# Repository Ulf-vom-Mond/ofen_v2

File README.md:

# Ofen v2
This is a project about building an oven for high temperatures. Included in this repository are the schematics and the layout for the control PCB and the microcontroller firmware.

## Building with Arduino IDE
You need to install the following libraries:

### LCDWiki library
This is neccessary for SPI communication with the ILI9488 LCD driver.
Follow this page for installation: http://www.lcdwiki.com/3.5inch_SPI_Module_ILI9488_SKU:MSP3520

### MiniCore
The schematic uses a bare ATMega328p without the Arduino overhead. For an effective use of all its features, you need to follow this installation guide:
https://github.com/MCUdude/MiniCore

IMPORTANT: You need to set the clock to "Internal 8 MHz". If you select anything called "external", the ATMega will not run and you cannot program it anymore.

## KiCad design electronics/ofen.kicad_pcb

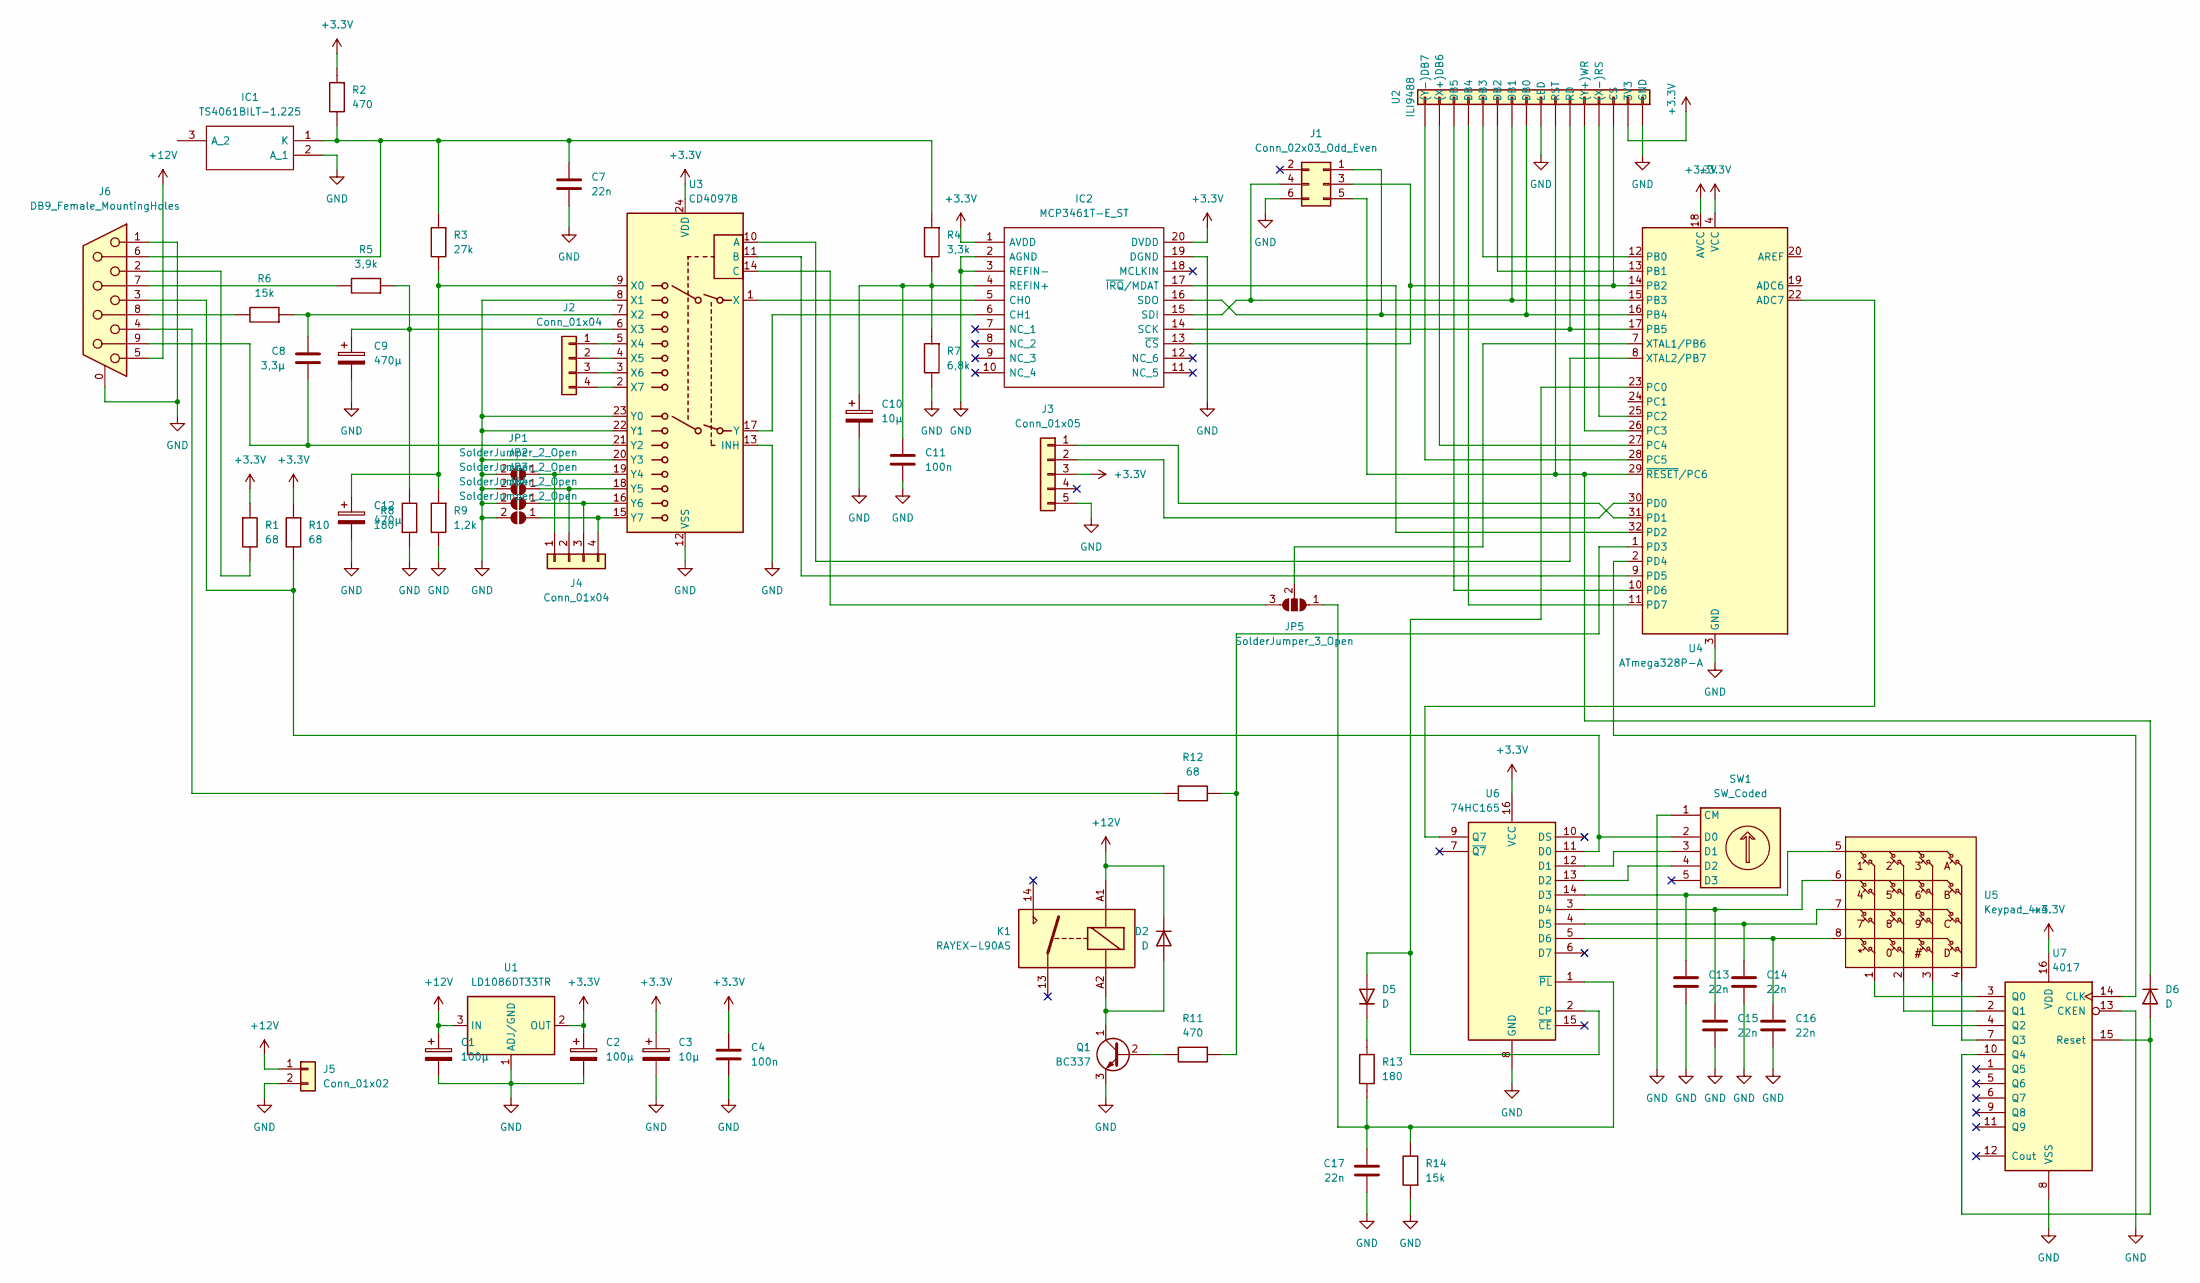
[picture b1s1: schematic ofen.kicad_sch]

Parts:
C1, C2: 100µ; CP_Radial_D6.3mm_P2.50mm
C3, C10: 10µ; CP_Radial_Tantal_D4.5mm_P5.00mm
C4, C11: 100n; C_Rect_L10.0mm_W4.0mm_P7.50mm_MKS4
C7, C13, C14, C15, C16, C17: 22n; C_Disc_D5.0mm_W2.5mm_P2.50mm
C8: 3,3µ; C_Rect_L7.2mm_W7.2mm_P5.00mm_FKS2_FKP2_MKS2_MKP2
C9, C12: 470µ; CP_Radial_D10.0mm_P5.00mm
D2, D5, D6: D; D_A-405_P7.62mm_Horizontal
IC1: TS4061BILT-1.225; SOT-23-3; Mouser Part Number 511-TS4061BILT-1.225
IC2: MCP3461T-E_ST; TSSOP-20_4.4x6.5mm_P0.65mm; Mouser Part Number 579-MCP3461T-E/ST
J1: Conn_02x03_Odd_Even; IDC-Header_2x03_P2.54mm_Vertical
J2, J4: Conn_01x04; PinHeader_1x04_P2.54mm_Vertical
J3: Conn_01x05; PinSocket_1x05_P2.54mm_Vertical
J5: Conn_01x02; JST_VH_B2P3-VH_1x02_P7.92mm_Vertical
J6: DB9_Female_MountingHoles; DSUB-9_Female_Horizontal_P2.77x2.84mm_EdgePinOffset7.70mm_H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
JP1, JP2, JP3, JP4: SolderJumper_2_Open; SolderJumper-2_P1.3mm_Open_RoundedPad1.0x1.5mm
JP5: SolderJumper_3_Open; SolderJumper-3_P1.3mm_Open_RoundedPad1.0x1.5mm_NumberLabels
K1: RAYEX-L90AS; Relay_SPST_RAYEX-L90AS
Q1: BC337; TO-92_Inline_Wide
R1, R10, R12: 68; R_Axial_DIN0207_L6.3mm_D2.5mm_P10.16mm_Horizontal
R2, R11: 470; R_Axial_DIN0207_L6.3mm_D2.5mm_P10.16mm_Horizontal
R3: 27k; R_Axial_DIN0207_L6.3mm_D2.5mm_P10.16mm_Horizontal
R4: 3,3k; R_Axial_DIN0207_L6.3mm_D2.5mm_P10.16mm_Horizontal
R5: 3,9k; R_Axial_DIN0207_L6.3mm_D2.5mm_P10.16mm_Horizontal
R6, R14: 15k; R_Axial_DIN0207_L6.3mm_D2.5mm_P10.16mm_Horizontal
R7: 6,8k; R_Axial_DIN0207_L6.3mm_D2.5mm_P10.16mm_Horizontal
R8, R13: 180; R_Axial_DIN0207_L6.3mm_D2.5mm_P10.16mm_Horizontal
R9: 1,2k; R_Axial_DIN0207_L6.3mm_D2.5mm_P10.16mm_Horizontal
SW1: SW_Coded; PinHeader_1x04_P2.54mm_Vertical
U1: LD1086DT33TR; SOT-223-3_TabPin2
U2: ILI9488; ribbon_1x17_vertical
U3: CD4097B; TSSOP-24_4.4x7.8mm_P0.65mm
U4: ATmega328P-A; TQFP-32_7x7mm_P0.8mm
U5: Keypad_4x4; Molex_Micro-Latch_53254-0870_1x08_P2.00mm_Horizontal
U6: 74HC165; TSSOP-16_4.4x5mm_P0.65mm
U7: 4017; DIP-16_W7.62mm

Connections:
+3.3V: C2.1, C3.1, C4.1, IC2.1 (AVDD), IC2.20 (DVDD), J3.3, R1.1, R2.1, R10.1, U1.2 (OUT), U2.2 (3V3), U3.24 (VDD), U4.4 (VCC), U4.6 (VCC), U4.18 (AVCC), U6.16 (VCC), U7.16 (VDD)
+12V: C1.1, D2.1 (K), J5.1, J6.5, K1.A1, U1.3 (IN)
GND: C1.2, C2.2, C3.2, C4.2, C7.2, C9.2, C10.2, C11.2, C12.2, C13.2, C14.2, C15.2, C16.2, C17.1, IC1.2 (A_1), IC2.2 (AGND), IC2.3 (REFIN-), IC2.19 (DGND), J1.6, J3.5, J5.2, J6.0 (PAD), J6.1, JP1.2 (B), JP2.2 (B), JP3.2 (B), JP4.2 (B), Q1.3 (E), R7.2, R8.1, R9.2, R14.1, SW1.1 (CM), U1.1 (ADJ/GND), U2.1 (GND), U2.8 (LED), U3.8 (X1), U3.12 (VSS), U3.13 (INH), U3.20 (Y3), U3.22 (Y1), U3.23 (Y0), U4.3 (GND), U4.5 (GND), U4.21 (GND), U6.8 (GND), U7.8 (VSS), U7.13 (CKEN)
unnamed: C7.1, IC1.1 (K), J6.6, R2.2, R3.1, R4.1
unnamed: C8.2, R6.1, U3.7 (X2)
unnamed: C9.1, R5.1, R8.2, U3.6 (X3)
unnamed: C10.1, C11.1, IC2.4 (REFIN+), R4.2, R7.1
unnamed: C12.1, R3.2, R9.1, U3.9 (X0)
unnamed: C13.1, U5.5, U6.14 (D3)
unnamed: C14.1, U5.7, U6.4 (D5)
unnamed: C15.1, U5.6, U6.3 (D4)
unnamed: C16.1, U5.8, U6.5 (D6)
unnamed: C17.2, JP5.1 (A), R13.2, R14.2, U6.1 (~PL)
unnamed: D2.2 (A), K1.A2, Q1.1 (C)
unnamed: D5.1 (K), R13.1
unnamed: D5.2 (A), U4.23 (PC0), U6.2 (CP)
unnamed: D6.1 (K), J1.5, U2.7 (RST), U4.29 (~RESET/PC6)
unnamed: D6.2 (A), U7.10 (Q4), U7.15 (Reset)
unnamed: IC2.5 (CH0), U3.1 (X)
unnamed: IC2.6 (CH1), U3.17 (Y)
unnamed: IC2.13 (~CS), J1.3, U2.3 (CS), U4.14 (PB2)
unnamed: IC2.14 (SCK), U2.6 (RD), U4.17 (PB5)
unnamed: IC2.15 (SDI), J1.4, U2.10 (DB1), U4.15 (PB3)
unnamed: IC2.16 (SDO), J1.1, U2.9 (DB0), U4.16 (PB4)
unnamed: IC2.17 (~IRQ/MDAT), U4.32 (PD2)
unnamed: J2.1, U3.5 (X4)
unnamed: J2.2, U3.4 (X5)
unnamed: J2.3, U3.3 (X6)
unnamed: J2.4, U3.2 (X7)
unnamed: J3.1, U4.31 (PD1)
unnamed: J3.2, U4.30 (PD0)
unnamed: J4.1, JP1.1 (A), U3.19 (Y4)
unnamed: J4.2, JP2.1 (A), U3.18 (Y5)
unnamed: J4.3, JP3.1 (A), U3.16 (Y6)
unnamed: J4.4, JP4.1 (A), U3.15 (Y7)
unnamed: Q1.2 (B), R11.2
unnamed: J6.2, R1.2
unnamed: J6.7, R5.2
unnamed: J6.8, R6.2
unnamed: J6.4, R12.1
unnamed: R11.1, R12.2, U4.1 (PD3)
unnamed: J6.3, R10.2, SW1.2 (D0), U6.11 (D0)
unnamed: SW1.3 (D1), U6.12 (D1)
unnamed: SW1.4 (D2), U6.13 (D2)
unnamed: U2.4 ((X-)RS), U4.25 (PC2)
unnamed: U2.5 ((Y+)WR), U4.26 (PC3)
unnamed: U2.11 (DB2), U4.13 (PB1)
unnamed: U2.12 (DB3), U4.12 (PB0)
unnamed: U2.13 (DB4), U4.11 (PD7)
unnamed: U2.14 (DB5), U4.10 (PD6)
unnamed: U2.15 ((X+)DB6), U4.27 (PC4)
unnamed: U2.16 ((Y-)DB7), U4.28 (PC5)
unnamed: U3.10 (A), U4.8 (XTAL2/PB7)
unnamed: U3.11 (B), U4.9 (PD5)
unnamed: JP5.3 (B), U3.14 (C)
unnamed: C8.1, J6.9, U3.21 (Y2)
unnamed: U4.2 (PD4), U7.14 (CLK)
unnamed: JP5.2 (C), U4.7 (XTAL1/PB6)
unnamed: U4.22 (ADC7), U6.9 (Q7)
unnamed: U5.1, U7.3 (Q0)
unnamed: U5.2, U7.2 (Q1)
unnamed: U5.3, U7.4 (Q2)
unnamed: U5.4, U7.7 (Q3)

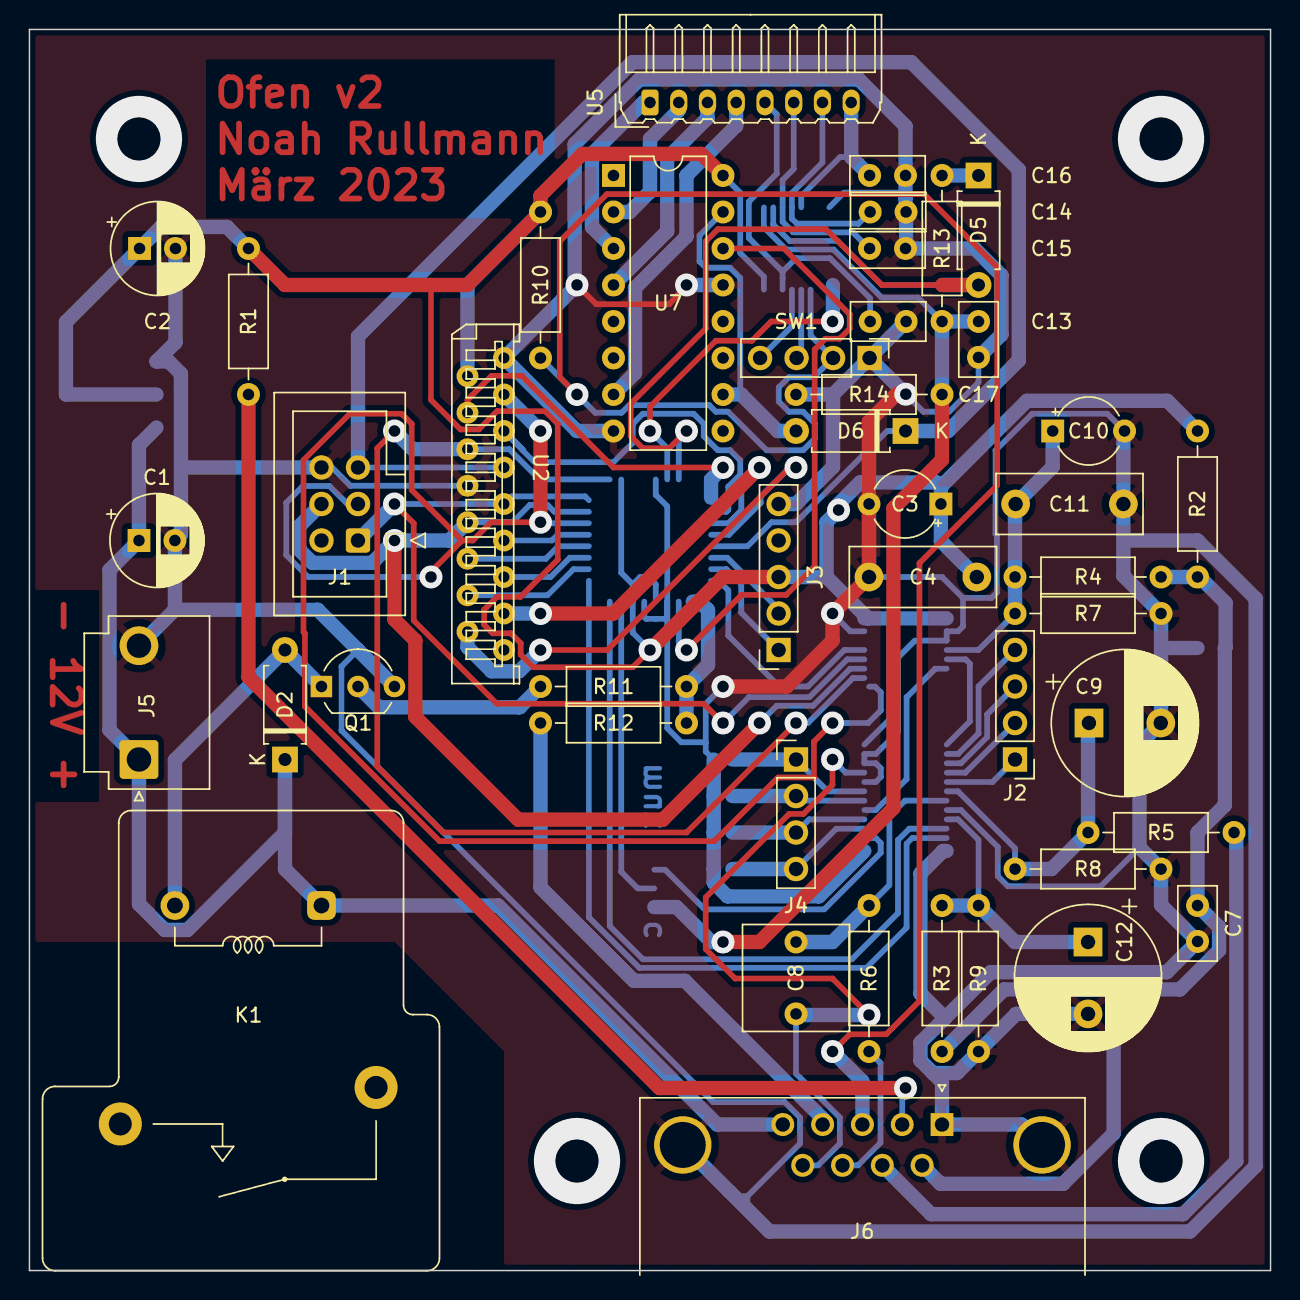
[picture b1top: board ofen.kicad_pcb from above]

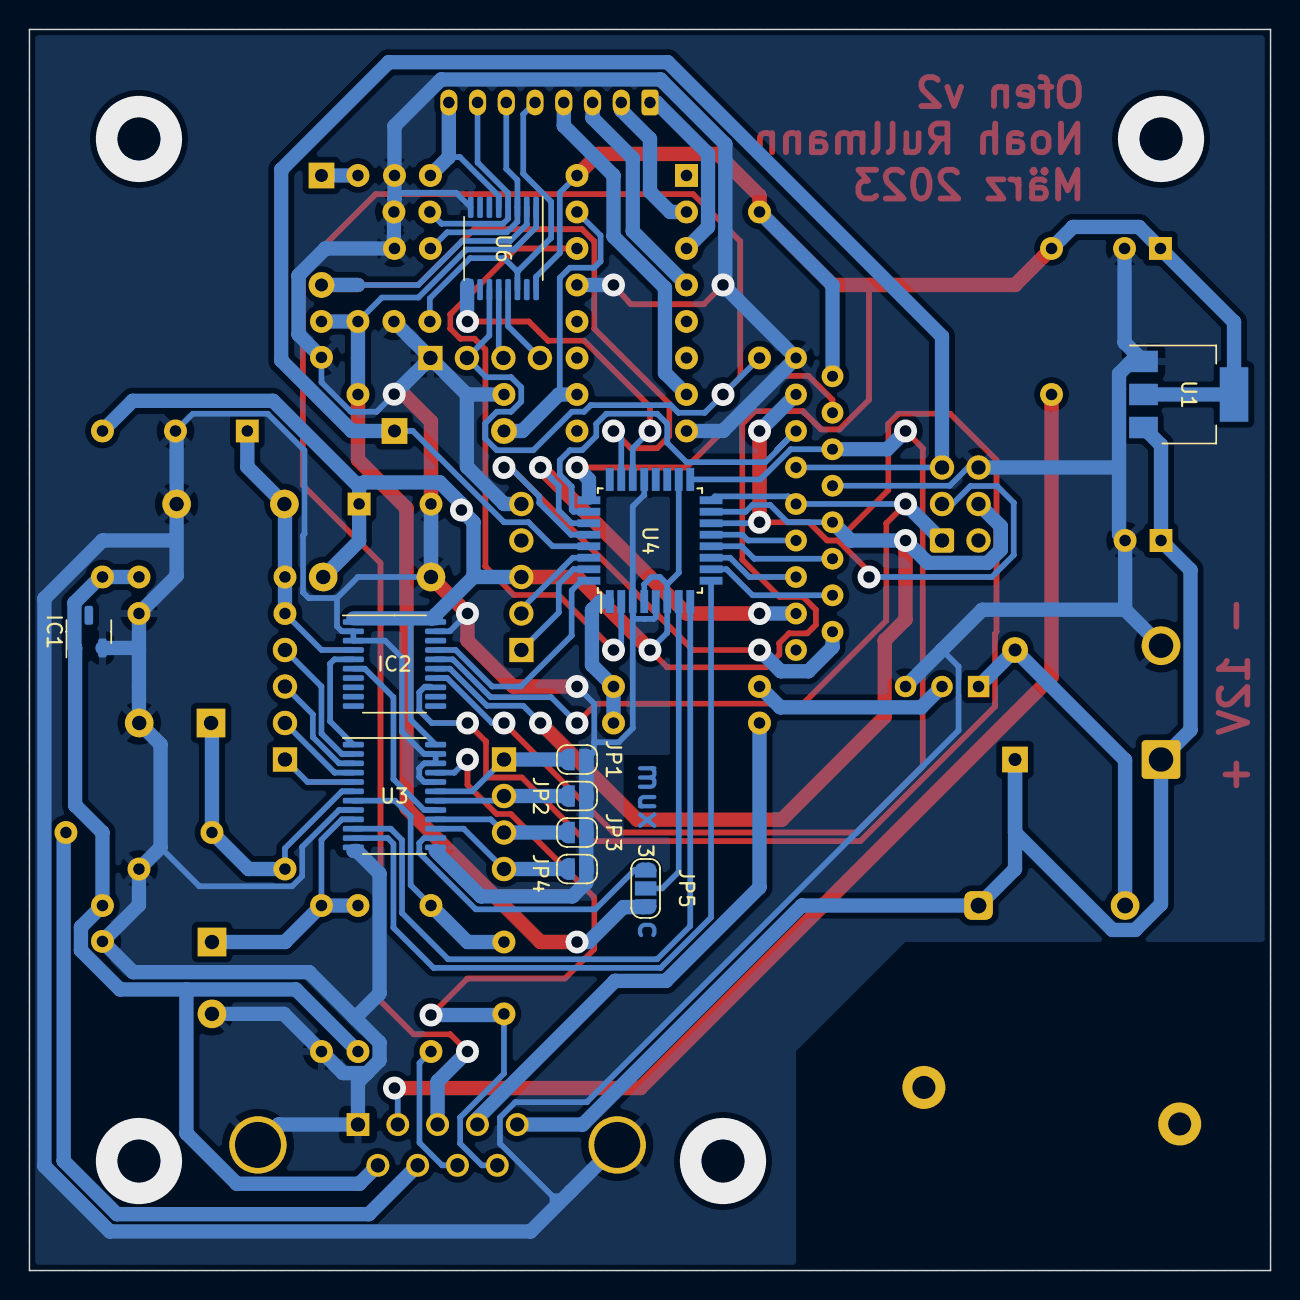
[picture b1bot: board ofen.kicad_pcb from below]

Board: 2 copper layers, 86.4 x 86.4 mm, 55 parts (11 on the bottom side), 63 nets.

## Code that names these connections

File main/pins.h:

#pragma once

#define IN  0
#define OUT 1

void pin_config();

// Pin definitions

// AVR pins get a number assigned according to the following scheme:
// The second decimal digit corresponds to the Port, starting at 0 for PORTA
// The first decimal digit corresponds to the Pin going from 0 thru 7
// Examples: PB5 is 15, PD6 is 36

// SD Card:
#define SD_CS_PIN       12 // PB2
#define SD_CS_DDR       OUT

// ILI9488 LCD:
#define LCD_CS_PIN      37 // PD7
#define LCD_CS_DDR      OUT
#define LCD_RST_PIN     10 // PB0
#define LCD_RST_DDR     OUT
#define LCD_DC_PIN      11 // PB1
#define LCD_DC_DDR      OUT

// XPT2046 Touch Controller:
#define TOUCH_CS_PIN    20 // PC0
#define TOUCH_CS_DDR    OUT
#define TOUCH_IRQ_PIN   32 // PD2
#define TOUCH_IRQ_DDR   IN

// MCP3461 ADC:
#define ADC_CS_PIN      21 // PC1
#define ADC_CS_DDR      OUT
#define ADC_IRQ_PIN     33 // PD3
#define ADC_IRQ_DDR     IN

// CD4097 Multiplexer:
#define MUX_A_PIN       24 // PC4
#define MUX_A_DDR       OUT
#define MUX_B_PIN       23 // PC3
#define MUX_B_DDR       OUT
#define MUX_C_PIN       22 // PC1
#define MUX_C_DDR       OUT

// CD4017 Demultiplexer:
#define DEMUX_A0_PIN    36 // PD6
#define DEMUX_A0_DDR    OUT
#define DEMUX_A1_PIN    35 // PD5
#define DEMIX_A1_DDR    OUT

// 74HC165 Shift Register:
#define SHIFT_Q_PIN     34 // PD4
#define SHIFT_Q_DDR     IN
#define SHIFT_CLK_PIN   17 // PB7
#define SHIFT_CLK_DDR   OUT
#define SHIFT_LOAD_PIN  16 // PB6
#define SHIFT_LOAD_DDR  OUT

// Heater Relais:
#define HEATER_PIN      25 // PC5
#define HEATER_DDR      OUT


// SPI:
#define MISO_PIN      14  
#define MISO_DDR      IN
#define MOSI_PIN      13
#define MOSI_DDR      OUT
#define SCK_PIN       15
#define SCK_DDR       OUT

// UART:
#define RX_PIN        30
#define RX_DDR        IN
#define TX_PIN        31
#define TX_DDR        OUT

// RESET
#define RST_PIN       26
#define RST_DDR       IN

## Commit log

2023-04-10 initial commit including version 2 of the oven PCB
2023-04-10 updated to version 2.1 of the pcb and added the first steps of the firmware
2023-04-11 solved initial errors
2023-04-14 added support for the keypad. only one key press can be recognized at a time.'
2023-04-17 added some basic graphics functionality
2023-04-17 add .gitignore
2023-04-19 splitted the graphics functions into multiple files and added some new ones
2023-04-20 fixed some warnings
2023-04-20 added a readme
2023-09-13 temperature table editing
2023-09-14 long press and multi click
2023-09-14 comments on keypad.cpp and user_interface.cpp
2023-09-14 restructured files
2023-09-23 started work on temp graph
2023-10-14 graph update works properly
2024-12-21 something changed with the kicad files?
2024-12-26 fixed adc issues, thermistor measurement works well now, still work to do with thermocouple
2024-12-27 broken commit, still need to save
2024-12-27 optimized flash usage, built async convert mechanism
2024-12-28 asynchronous thermistor measurement works in most of the cases
2024-12-28 thermistor measurement works perfectly
2024-12-28 thermocouple temperature calculation seems to work, but some problem is still present
2024-12-29 print thermistor temperature to lcd
